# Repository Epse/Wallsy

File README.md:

# Wallsy
Firmware for a hacked Disney U-Control Wall-e

## What the frig is this?
Me and someone without a github replaced the logic board in a U-Control Wall-e with a [Teensy LC](https://www.pjrc.com/teensy/teensyLC.html).
We added a distance sensor (a Sharp optical ridiculously expensive one since the Chinese ultrasonic cheap ones wouldn't arrive in time)
and a yellow LED in the middle of the sun on Wall-e's 'display'.

## Why would you do that?
It's fun!

## How do I use this?
Get a Teensy, wire it up, modify the `#define`'s in the `main.ino` file and upload to the Teensy.
That is, if your Arduino IDE has the [Teensy libraries](https://www.pjrc.com/teensy/teensyduino.html) installed.

## What works and what doesn't?
- [ ] motor control
- [x] LED blinking
- [ ] IR control
- [ ] Sounds
- [ ] Distance sensing

Yes, for now you let it run by programming moves...

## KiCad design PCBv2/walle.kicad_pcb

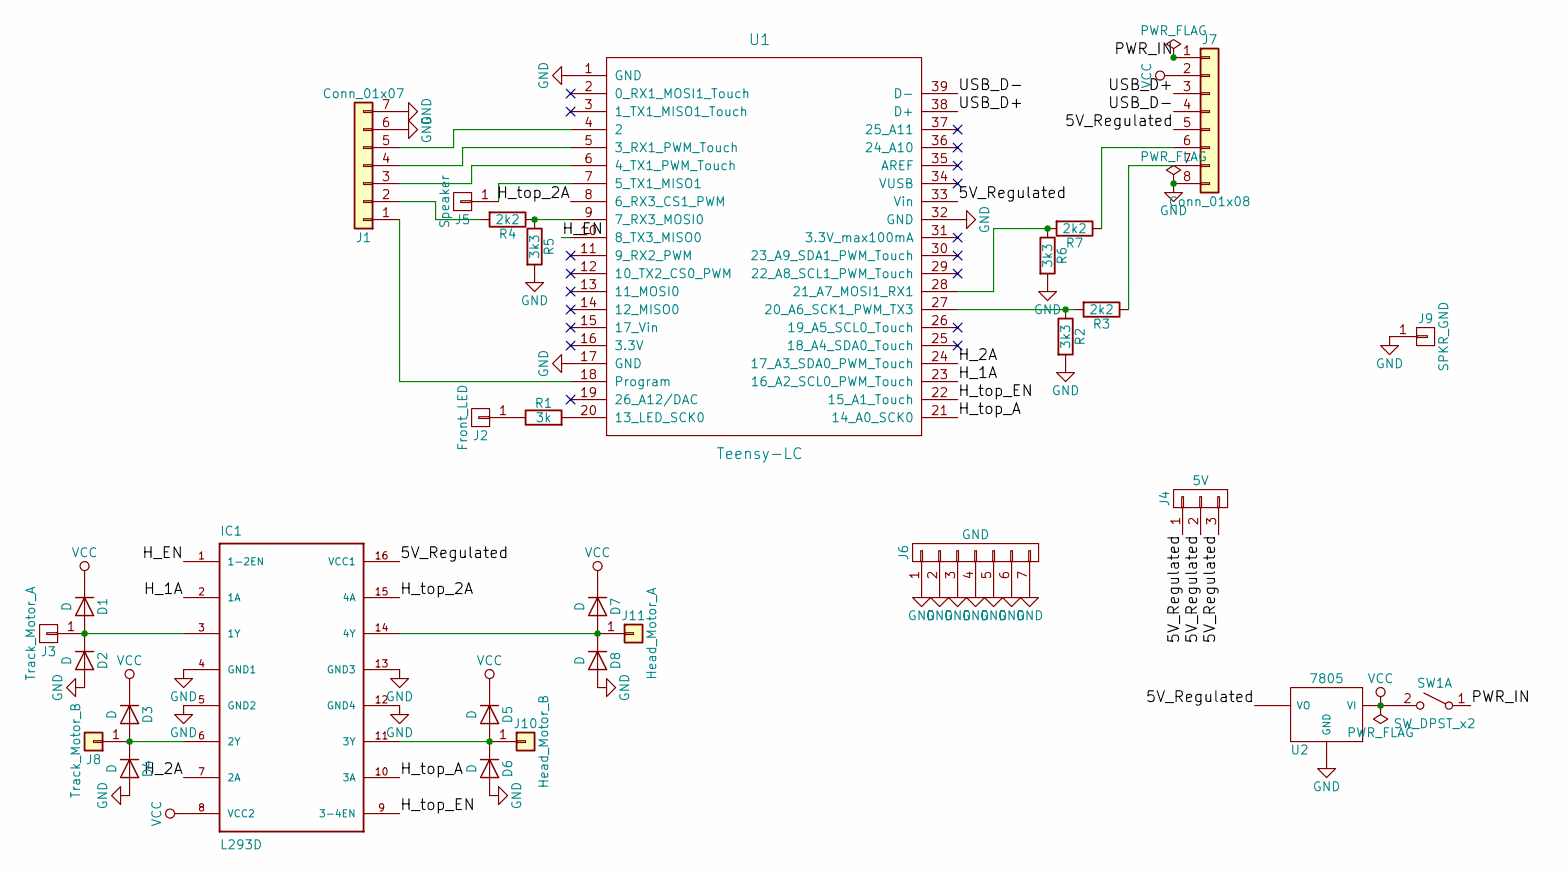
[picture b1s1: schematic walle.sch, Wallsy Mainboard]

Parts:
D1, D2, D3, D4, D5, D6, D7, D8: D; D_A-405_P2.54mm_Vertical_AnodeUp
IC1: L293D; DIL16
J1: Conn_01x07; Pin_Header_Straight_1x07_Pitch2.54mm
J2: Front_LED; Pin_Header_Straight_1x01_Pitch2.54mm
J3: Track_Motor_A; Pin_Header_Straight_1x01_Pitch2.54mm
J4: 5V; Pin_Header_Straight_1x03_Pitch2.54mm
J5: Speaker; Pin_Header_Straight_1x01_Pitch2.54mm
J6: GND; Pin_Header_Straight_1x07_Pitch2.54mm
J7: Conn_01x08; Pin_Header_Straight_1x08_Pitch2.54mm
J8: Track_Motor_B; Pin_Header_Straight_1x01_Pitch2.54mm
J9: SPKR_GND; Pin_Header_Straight_1x01_Pitch2.54mm
J10: Head_Motor_B; Pin_Header_Straight_1x01_Pitch2.54mm
J11: Head_Motor_A; Pin_Header_Straight_1x01_Pitch2.54mm
R1: 3k; R_Axial_DIN0204_L3.6mm_D1.6mm_P1.90mm_Vertical
R2, R5, R6: 3k3; R_Axial_DIN0204_L3.6mm_D1.6mm_P1.90mm_Vertical
R3, R4, R7: 2k2; R_Axial_DIN0204_L3.6mm_D1.6mm_P1.90mm_Vertical
SW1: SW_DPST_x2; Pin_Header_Straight_1x02_Pitch2.54mm
U1: Teensy-LC; Teensy30_31_32_LC
U2: 7805; TO-220

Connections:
/5V_Regulated: IC1.16 (VCC1), J4.1, J4.2, J4.3, J7.5, U1.33 (Vin), U2.3 (VO)
/H_1A: IC1.2 (1A), U1.23 (16_A2_SCL0_PWM_Touch)
/H_2A: IC1.7 (2A), U1.24 (17_A3_SDA0_PWM_Touch)
/H_EN: IC1.1 (1-2EN), U1.10 (8_TX3_MISO0)
/H_top_2A: IC1.15 (4A), U1.8 (6_RX3_CS1_PWM)
/H_top_A: IC1.10 (3A), U1.21 (14_A0_SCK0)
/H_top_EN: IC1.9 (3-4EN), U1.22 (15_A1_Touch)
/PWR_IN: J7.1, SW1.1 (A)
/USB_D+: J7.3, U1.38 (D+)
/USB_D-: J7.4, U1.39 (D-)
GND: D2.2 (A), D4.2 (A), D6.2 (A), D8.2 (A), IC1.4 (GND1), IC1.5 (GND2), IC1.12 (GND4), IC1.13 (GND3), J1.6, J1.7, J6.1, J6.2, J6.3, J6.4, J6.5, J6.6, J6.7, J7.8, J9.1, R2.2, R5.2, R6.2, U1.1 (GND), U1.17 (GND), U1.32 (GND), U2.2 (GND)
unnamed: D1.2 (A), D2.1 (K), IC1.3 (1Y), J3.1
unnamed: D3.2 (A), D4.1 (K), IC1.6 (2Y), J8.1
unnamed: D5.2 (A), D6.1 (K), IC1.11 (3Y), J10.1
unnamed: D7.2 (A), D8.1 (K), IC1.14 (4Y), J11.1
unnamed: J1.1, U1.18 (Program)
unnamed: J1.2, R4.2
unnamed: J1.3, U1.6 (4_TX1_PWM_Touch)
unnamed: J1.4, U1.5 (3_RX1_PWM_Touch)
unnamed: J1.5, U1.4 (2)
unnamed: J2.1, R1.1
unnamed: J5.1, U1.7 (5_TX1_MISO1)
unnamed: J7.6, R7.1
unnamed: J7.7, R3.1
unnamed: R1.2, U1.20 (13_LED_SCK0)
unnamed: R2.1, R3.2, U1.27 (20_A6_SCK1_PWM_TX3)
unnamed: R4.1, R5.1, U1.9 (7_RX3_MOSI0)
unnamed: R6.1, R7.2, U1.28 (21_A7_MOSI1_RX1)
unnamed: SW1.2 (B), U2.1 (VI)
VCC: D1.1 (K), D3.1 (K), D5.1 (K), D7.1 (K), IC1.8 (VCC2), J7.2

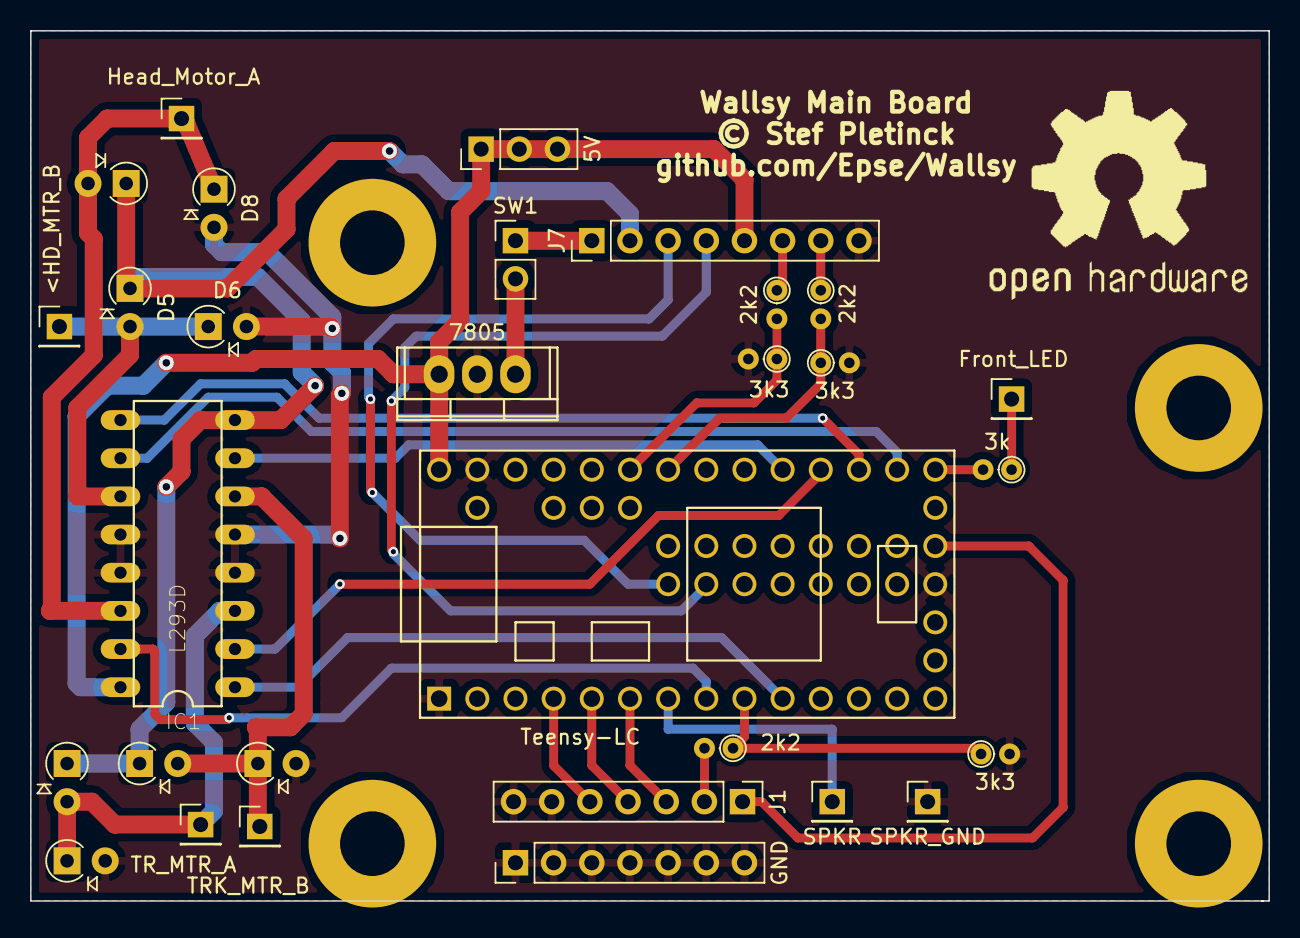
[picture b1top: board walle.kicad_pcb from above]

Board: 2 copper layers, 82.4 x 57.9 mm, 30 parts (0 on the bottom side), 30 nets.

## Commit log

2017-08-04 framework
2017-08-04 motor framework
2017-08-04 im a retard
2017-08-04 its been way too long
2017-08-15 Split out into multiple files
2017-08-15 Added readme
2017-08-15 Added dispatchers and simple status blinker
2017-08-15 I have been a moron. This now works.
2017-08-30 Placeholder / test feature for the button and the LED\'s
2017-08-30 he seems so dead otherwise
2017-08-30 Why were those lines there?
2017-09-23 updates, but it bricked the teensy
2017-09-24 The front button will be wired up to the program pin
2017-09-25 Gave speaker high current pin
2017-09-27 added KiCAD project for PCB
2017-10-09 PCB redesign for 1 h-bridge
2017-10-09 better pcb
2017-10-11 assigned footprints
2017-10-11 ratsnest
2017-10-16 final PCB

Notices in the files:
PCBv2/walle.kicad_pcb:
© Stef Pletinck
